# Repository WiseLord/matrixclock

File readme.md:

# Matrixclock

This project is a simple LED matrix clock. It can use either MAX7219 as LED drivers (one IC per matrix) either HT1632 LED driver. It's possible to use 3 or 4 matrixes, but recent code is more suitable for second option.

There is a [video](https://youtu.be/mCT93ut2W2s) on Youtube about this.

# Main features:

* RTC DS1307 support (DS3231 also works)
* One alarm which can be enabled for any day of week
* Active beeper is used for alarm and signals
* Temperature measurement with DS18B20 sensors
* Pressure/temperature measurement with BMP180 sensor
* Humidity/temperature measurement with DHT22 sensor
* Scrolling date and sensors data strings
* Reducing brigtness in darkness

# Supported LED drivers:

* MAX7219 (one per LED matrix). Pinout and schematic are [here](files/schematic.png)
* HT1632 (one for 4 matrixes). Pinout for _JY-MCU 3208CLOCK PRO_ module

# Matrixclock EEPROM editor

While project uses various parameters from EEPROM memory special desktop application to edit eeprom matrixclock_xx.bin was designed. It allows to load, modify and save eeprom binary file in easy way.

Matrixclock editor is written on Qt5 and it's sources are availiable [here](editor).

# Useful links:

* [Article about the project](http://radiokot.ru/circuit/digital/home/206) (in Russian)
* [Forum thread](http://radiokot.ru/forum/viewtopic.php?t=112934) (in Russian)

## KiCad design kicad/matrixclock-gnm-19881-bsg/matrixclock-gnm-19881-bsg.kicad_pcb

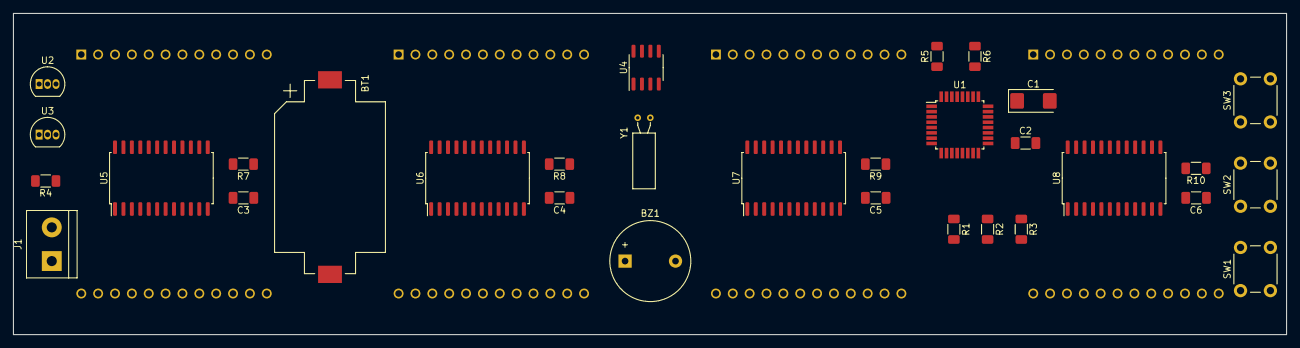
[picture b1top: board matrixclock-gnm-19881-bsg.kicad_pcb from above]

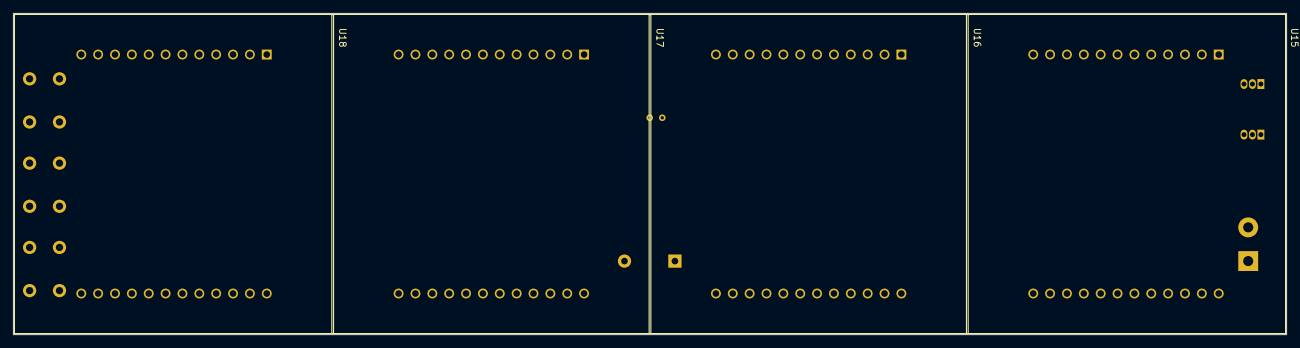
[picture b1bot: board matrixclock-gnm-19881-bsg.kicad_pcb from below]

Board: 2 copper layers, 191.8 x 48.4 mm, 35 parts (4 on the bottom side), 86 nets, no tracks yet.

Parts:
BT1: Li_3.3V; BatteryHolder_Keystone_1060_1x2032
BZ1: Buzzer; Buzzer_12x9.5RM7.6
C1: 100.0; CP_EIA-6032-28_Kemet-C
C2, C3, C4, C5, C6: 0.1; C_1206_3216Metric_Pad1.33x1.80mm_HandSolder
J1: PWR; TerminalBlock_bornier-2_P5.08mm
R1, R2, R3, R7, R8, R9, R10: 10k; R_1206_3216Metric_Pad1.30x1.75mm_HandSolder
R4, R5, R6: 4k7; R_1206_3216Metric_Pad1.30x1.75mm_HandSolder
SW1: MENU; SW_PUSH_6mm
SW2: INC; SW_PUSH_6mm
SW3: DEC; SW_PUSH_6mm
U1: ATmega328P-AU; TQFP-32_7x7mm_P0.8mm
U2, U3: DS18B20; TO-92_Inline
U4: DS1307Z+; SOIC-8_3.9x4.9mm_P1.27mm
U5, U6, U7, U8: MAX7219; SOIC-24W_7.5x15.4mm_P1.27mm
U15, U16, U17, U18: GNM-19881-BSG
Y1: 32768; Crystal_C38-LF_D3.0mm_L8.0mm_Horizontal

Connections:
+5VD: BZ1.1, C1.1, C2.1, C3.1, C4.1, C5.1, C6.1, J1.2, R1.1, R2.1, R3.1, R4.1, R5.1, R6.1, R7.1, R8.1, R9.1, R10.1, U1.4, U1.6, U1.18, U1.20, U2.3, U3.3, U4.8, U5.19, U6.19, U7.19, U8.19
/BTN1: R1.2, SW1.1, U1.15
/BTN2: R2.2, SW2.1, U1.16
/BTN3: R3.2, SW3.1, U1.17
/BUZZ: BZ1.2, U1.9
/CLK: U1.31, U5.13, U6.13, U7.13, U8.13
/DIN: U1.30, U5.1
/DQ: R4.2, U1.10, U2.2, U3.2
/LOAD: U1.2, U5.12, U6.12, U7.12, U8.12
/SCL: R6.2, U1.28, U4.6
/SDA: R5.2, U1.27, U4.5
/mxblock1/D0: U5.2, U15.24
/mxblock1/D1: U5.11, U15.3
/mxblock1/D2: U5.6, U15.21
/mxblock1/D3: U5.7, U15.6
/mxblock1/D4: U5.3, U15.18
/mxblock1/D5: U5.10, U15.9
/mxblock1/D6: U5.5, U15.15
/mxblock1/D7: U5.8, U15.12
/mxblock1/S0: U5.22, U15.10
/mxblock1/S1: U5.14, U15.13
/mxblock1/S2: U5.16, U15.7
/mxblock1/S3: U5.20, U15.16
/mxblock1/S4: U5.23, U15.4
/mxblock1/S5: U5.21, U15.19
/mxblock1/S6: U5.15, U15.1
/mxblock1/S7: U5.17, U15.22
/mxblock2/D0: U6.2, U16.24
/mxblock2/D1: U6.11, U16.3
/mxblock2/D2: U6.6, U16.21
/mxblock2/D3: U6.7, U16.6
/mxblock2/D4: U6.3, U16.18
/mxblock2/D5: U6.10, U16.9
/mxblock2/D6: U6.5, U16.15
/mxblock2/D7: U6.8, U16.12
/mxblock2/DIN: U5.24, U6.1
/mxblock2/S0: U6.22, U16.10
/mxblock2/S1: U6.14, U16.13
/mxblock2/S2: U6.16, U16.7
/mxblock2/S3: U6.20, U16.16
/mxblock2/S4: U6.23, U16.4
/mxblock2/S5: U6.21, U16.19
/mxblock2/S6: U6.15, U16.1
/mxblock2/S7: U6.17, U16.22
/mxblock3/D0: U7.2, U17.24
/mxblock3/D1: U7.11, U17.3
/mxblock3/D2: U7.6, U17.21
/mxblock3/D3: U7.7, U17.6
/mxblock3/D4: U7.3, U17.18
/mxblock3/D5: U7.10, U17.9
/mxblock3/D6: U7.5, U17.15
/mxblock3/D7: U7.8, U17.12
/mxblock3/DIN: U6.24, U7.1
/mxblock3/S0: U7.22, U17.10
/mxblock3/S1: U7.14, U17.13
/mxblock3/S2: U7.16, U17.7
/mxblock3/S3: U7.20, U17.16
/mxblock3/S4: U7.23, U17.4
/mxblock3/S5: U7.21, U17.19
/mxblock3/S6: U7.15, U17.1
/mxblock3/S7: U7.17, U17.22
/mxblock4/D0: U8.2, U18.24
/mxblock4/D1: U8.11, U18.3
/mxblock4/D2: U8.6, U18.21
/mxblock4/D3: U8.7, U18.6
/mxblock4/D4: U8.3, U18.18
/mxblock4/D5: U8.10, U18.9
/mxblock4/D6: U8.5, U18.15
/mxblock4/D7: U8.8, U18.12
/mxblock4/DIN: U7.24, U8.1
/mxblock4/S0: U8.22, U18.10
/mxblock4/S1: U8.14, U18.13
/mxblock4/S2: U8.16, U18.7
/mxblock4/S3: U8.20, U18.16
/mxblock4/S4: U8.23, U18.4
/mxblock4/S5: U8.21, U18.19
/mxblock4/S6: U8.15, U18.1
/mxblock4/S7: U8.17, U18.22
GNDD: BT1.2, C1.2, C2.2, C3.2, C4.2, C5.2, C6.2, J1.1, SW1.2, SW2.2, SW3.2, U1.3, U1.5, U1.21, U2.1, U3.1, U4.4, U5.4, U5.9, U6.4, U6.9, U7.4, U7.9, U8.4, U8.9
unnamed: BT1.1, U4.3
unnamed: R7.2, U5.18
unnamed: R8.2, U6.18
unnamed: R9.2, U7.18
unnamed: R10.2, U8.18
unnamed: U4.1, Y1.1
unnamed: U4.2, Y1.2

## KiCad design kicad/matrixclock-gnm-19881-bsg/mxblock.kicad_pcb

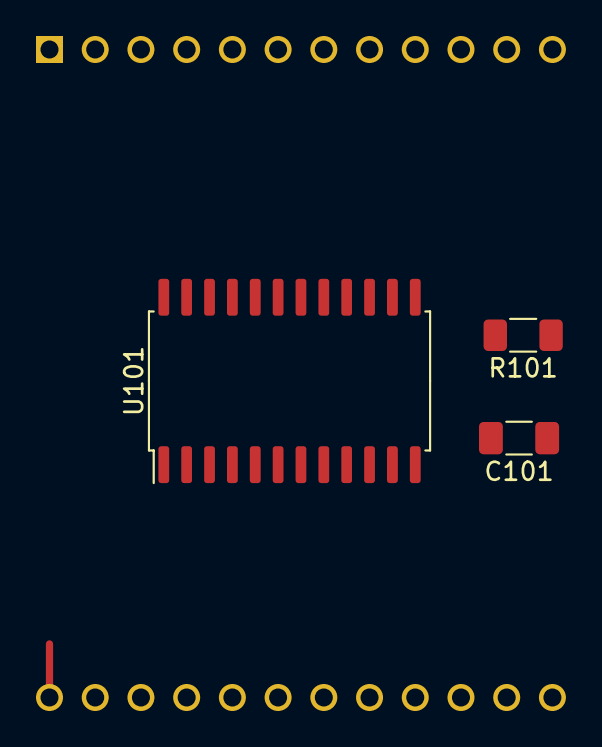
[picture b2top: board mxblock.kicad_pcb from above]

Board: 2 copper layers, 4 parts (1 on the bottom side), 19 nets.

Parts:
C101: 0.1; C_1206_3216Metric_Pad1.33x1.80mm_HandSolder
R101: 10k; R_1206_3216Metric_Pad1.30x1.75mm_HandSolder
U101: MAX7219; SOIC-24W_7.5x15.4mm_P1.27mm
U102: GNM-19881-BSG

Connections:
+5VD: C101.1, R101.1, U101.19
/D0: U101.2, U102.24
/D1: U101.11, U102.3
/D2: U101.6, U102.21
/D3: U101.7, U102.6
/D4: U101.3, U102.18
/D5: U101.10, U102.9
/D6: U101.5, U102.15
/D7: U101.8, U102.12
/S0: U101.22, U102.10
/S1: U101.14, U102.13
/S2: U101.16, U102.7
/S3: U101.20, U102.16
/S4: U101.23, U102.4
/S5: U101.21, U102.19
/S6: U101.15, U102.1
/S7: U101.17, U102.22
GNDD: C101.2, U101.4, U101.9
unnamed: R101.2, U101.18

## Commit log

2014-08-24 Added DS1307 RTC IC support.
2014-08-24 Real date output.
2014-08-24 Added support of DS18X20 temperature sensors.
2014-08-30 Code refactoring.
2014-08-30 String type changed from uint8_t to char.
2014-08-30 Switch to pgmspace strings.
2014-08-30 Hardware beeper.
2014-08-30 Hardware scroll based on timers instead of delays.
2014-08-30 Buttons polling added.
2014-08-30 Beep on commands.
2014-08-30 Buttons handling in main mode.
2014-08-30 Time edit mode.
2014-08-30 Text labels for editable params.
2014-08-30 Alarm support added.
2014-08-31 Per-hour brightness support.
2014-08-31 Screen rotate feature.
2015-01-26 Code refactoring and sync with other projects.
2015-01-26 Fix comma position.
2015-02-03 Changes in Makefile.
2015-02-03 Change code for several MAX7219 connected to chain. Control with 3 lines only.
2015-02-03 Optimize buttons behaviour.
2015-02-03 Small changes in EEPROM.
2015-02-03 Code optimizations and refactoring.
2015-02-04 Fix DS18x20 timings for been working in Proteus similator.
2015-02-04 Fix year string output.
2015-04-24 Compiler flags optimization.
2015-04-24 Fix typo in comment.
2015-04-29 Ouptut on 4 matrixes.
2015-04-29 Seconds on 4rd matrix.
2015-04-29 Change eeprom extention from .eep to .bin.
2015-04-29 Fix initial timemask.
2015-04-30 Rename max7219 to matrix.
2015-04-30 MAX7219 code refactoring.
2015-04-30 Separate eeprom and pins defines.
2015-04-30 HT1632 led driver support.
2015-05-01 Add software I2C pins definitions
2015-05-01 DS1307 code refactoring.
2015-05-01 Switch to software I2C.
2015-05-01 Code refactoring and optimizations.
2015-05-01 Set RAM buffer size to 384 bytes.
2015-05-03 Code refactoring. Fix scroll bug.
2015-05-03 Makefile changes.
2015-05-04 Fix eeprom file name in Makefile.
2015-05-04 Code refactoring (mask defines).
2015-05-04 Optimize reading time.
2015-05-05 Fix edit time.
2015-05-05 Move text labels to EEPROM.
2015-05-05 Ability to build for ATmega88/168/328.
2015-05-05 Remove charset selection from Makefile.
2015-05-05 Set BODLEVEL to 4V.
2015-05-05 Ability to use custom font in EEPROM with 5px width.
2015-05-05 Optimize font, remove unneeded symbols.
2015-05-05 Set non-custom font as default.
2015-05-06 Switch to main screen when changing font.
2015-05-06 Screen rotate feature returned.
2015-05-06 Optimize brightness handling.
2015-05-06 Fix russian eeprom file.
2015-05-06 Fix entering edit time/alarm mode.
2015-05-06 Beep every hour.
2015-05-07 Switch to CP1251 encoding.
2015-05-07 Fix Belarusian eeprom.
2015-05-07 Fix some text labels.
2015-05-07 Shorter hour beep.
2015-05-07 Code optimizations and fixes.
2015-05-07 Hour beeper start works later then alarm.
2015-05-07 Fix 0 hour brightness level corruption op power on.
2015-05-08 USE avr-libc crc8 calculation implementation.
2015-05-08 Optimize crc calculation.
2015-05-08 Added UA localization. ATmega88 added to build script.
2015-05-08 Set delays to values recommended by AVR318 appnote.
2015-05-23 Code cleanup and refactoring.
2015-05-28 Add extra big numbers.
2015-05-28 Switch hour leading zero by 1-2 long button press.
2015-05-28 Optimization of showTime function.
2015-05-28 Disappearing effect before scroll.
2015-05-29 Added support of MAX7219-based modules, where 90deg rotate is needed.
2015-05-30 Optimizations in DS18x20 driver.
2015-05-30 Optimizations and refacroting in software I2C.
2015-05-30 Added measuring ADC level (future brightness).
2015-05-30 Calculate brightness hour instead of read from EEPROM.
2015-05-30 Added photoresistor support (like MJ356, 5..10kOhm).
2015-06-02 Set brightness to signed type for proper calculating by forumela.
2015-06-19 Fix temp calculation for DS18S20/DS1820.
2015-06-19 Move spaces from eeprom to code.
2015-06-19 Added some more strings to eeprom for future pressure/humidity measurements.
2015-06-19 Show temperature label.
2015-06-20 Optimize DS18x20 driver.
2015-06-20 Refactoring RTC/alarm to fit Proteus.
2015-06-20 DS1307: use struct instead of array.
2015-06-20 Use global time variable.
2015-06-20 Small refactoring.
2015-06-20 Small alarm refactoring and cleanup.
2015-06-20 DS1307 code refactoring and optimization.
2015-06-20 Rename DS1307 to RTC.
2015-06-20 Small rtc code cleanup.
2015-06-20 Move min/max values of RTC params to program memory.
2015-06-20 Initial alarm refactoring.
2015-06-20 Alarm code refactoring.
2015-06-20 Matrix code optimization.
2015-06-20 Optimize work with masks.
2015-06-20 Scroll mode refactoring.
2015-06-21 Fix show time on power on.
2015-06-21 Fix space near year.
2015-06-21 Mask handling refactoring.
2015-06-21 Remove alarm screen.
2015-06-21 Barometric sensor bmp180 support.
2015-06-21 Some fixes and improvements.
2015-06-21 Fix brightness auto control.
2015-06-22 Fix output hours with hourZero enabled.
2015-06-22 Remove unused byte in main font.
2015-06-22 Extend time output when use extrabig font.
2015-06-23 Fix saving alarm.
2015-06-23 Output scrolling strings every minute.
2015-06-25 Builds for 3 x MAX7219 system.
2015-06-26 Fast temperature measure on start.
2015-06-26 Fix brightness when no photoresistor installed.
2015-06-26 Take ADCH value only one time instead of three.
2015-06-26 Small code cleanup and refactoring.
2015-06-26 Fix stop scrolling.
2015-07-08 Small code optimizations.
2015-07-08 Refactoring digits change.
2015-07-08 Refactoring showColon() function.
2015-07-08 Change code calculation mask bits.
2015-07-08 Added DHT22 support.
2015-07-09 Fix pinout for MAX7219MOD.
2015-07-09 Optimize calculating rtcDaysInMonth() function.
2015-07-09 Optimize timers and ADC.
2015-07-09 Small code optimization.
2015-07-10 Longer output string support.
2015-07-10 Don't overload strBuf array.
2015-07-14 Small optimize by size MAX7219 drivers.
2015-07-14 Small optimize by size HT1632 drivers.
2015-07-14 Return output "Temperature" word.
2015-07-14 Smooth brightness control and filter noise.
2015-07-14 Ouptupt of sensor data from DHT22/BMP180 can be disabled.
2015-07-14 Fix build for three MAX7219 option.
2015-07-14 Miminal photoresistor level detectinon.
2015-07-16 Optimize timers.
2015-07-16 Optimize buttons polling code. Buttons can be used only on the same port.
2015-07-16 Scroll interval can be set in EEPROM ad 0x0D offset.
2015-07-18 Change button 1 behaviour.
2015-07-18 Optimize edit parameters.
2015-07-19 Added second option for ready china modules.
2015-07-26 Optimize BTN1 behaviour.
2015-07-26 Optimize buttons long press behaviour.
2015-07-26 Optimize BTN2/BTN3 behaviour.
2015-07-27 Fix minutes label when tuning alarm.
2015-08-23 Eeprom defines refactoring.
2015-09-01 Switch raw weekday type from int8_t to uint8_t
2015-09-07 editor: Initial files.
2015-09-07 editor: Add cp1251 encoding.
2015-09-07 editor: add some more parameters.
2015-09-07 editor: Added other parameters.
2015-09-07 editor: Fix eeprom font corruption.
2015-09-10 editor: Inverse hourzero function.
2015-09-10 Hourzero refactoring.
2015-09-10 Change some default EEPROM values.
2015-09-11 editor: EEPROM fonts editing feature
2015-09-11 editor: alarm support
2015-09-11 editor: Fix typo
2015-09-11 Ability to switch off every hour signal
2015-09-12 Fix alarm and hourclock indication.
2015-09-12 Fix font switch on MOD2_X3
2015-09-12 Better colon and alarm indicator switch look-n-feel
2015-09-15 Fix hour signal.
2015-09-30 Optimize brightness limits.
2015-09-30 Reset seconds to 0 when edit them. Fix freeze time during edit.
2015-09-30 Sync DS18x20 driver with ampcontrol project to save some RAM
2015-10-01 Makefile refactoring.
2015-11-07 Fix Makefile
2015-11-08 Small code size optimize
2015-11-08 Implementation of new string buffer
2015-11-08 Fix clearing screen before scroll and zeroing first column
2015-11-25 Add some useful files
2015-11-28 Fix in codepage convertor (sync with ampcontrol)
2015-12-16 Simplify size.sh
2016-02-06 Fix weekday calculating on change date
2016-02-06 Increase threshold on photoresistor level
2016-04-01 Refactoring comments style
2016-04-02 Some code refactoring
2016-04-02 Refactoring bignum enum
2016-04-02 Leave only normal and big fonts (different for 3x and 4x matrix
2016-04-02 Remove screen rotate with 1-2-3 buttons feature
2016-04-02 Refactored alarm
2016-04-02 Alarm duration now is read from eeprom
2016-08-08 Update proteus project
2016-08-08 Refactoring input
2016-08-08 Refactoring some timers
2016-08-08 Refactored alarm timer
2016-08-09 Refactoring 3 or 4 matrixes selection
2016-08-09 Removed rotate feature and mods
2016-08-09 Test mode added
2016-08-09 Small optimize DS18x20 code
2016-08-09 8 values of rotate
2016-08-09 Refactoring access to framebuffer
2016-08-10 Rotate 90 degrees feature
2016-08-10 Changed eeprom layout
2016-08-10 Optimize work with eeprom
2016-08-10 Change default eeprom values
2016-08-10 Updated eeprom editor
2016-08-10 Update Proteus project files
2016-08-10 Code optimizations
2016-08-11 Some more optimization of work with eeprom
2016-12-19 Fixed scroll interval values > 127
2017-04-23 Modify compiler flags for smaller flash size
2017-08-08 Use scrollTimer=0 as value for stopping autoScroll
2017-10-31 Fix Feb days calculation.
2018-03-03 Seconds correction support
2018-03-03 corr
2018-03-03 -- correction mode
2018-03-03 editor: support seconds correction
2018-03-03 Small code optimization
2018-03-04 Makefile and defines refactoring
2018-03-04 Code restyle via astyle
2018-03-04 Refactor pins definitions
2018-03-08 Fix build for MAX7219
2018-03-12 Do seconds correction once a week
2018-03-12 Update binary files
2018-03-12 Russian translation of eeprom editor
2018-03-12 editor: switch language on the fly
2018-03-12 Added Belarusian translation
2018-03-12 editor: Code restyle
2018-05-16 Return big font on 4x option
2018-08-04 Optimize direction handling
2018-08-21 Small optimize to fit 8kB ATmega8
2018-11-17 Mod 6 x 5x8
2020-04-30 Optimize bignum
2020-05-01 Some size-related optimizaton
2020-05-01 Make eeprom struct non-extern
2020-11-08 Prepare KiCad project skeleton for GNM-19981-BSG
2020-11-08 Move the project to src subdir
2020-11-08 Add schematic and basic PCB skeleton
2022-01-22 Rework project file structure
2022-01-22 Add readme.md
